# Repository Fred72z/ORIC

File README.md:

# BUS ORIC

Ensemble de platines pouvant se connecter sur un boitier principal connecté au port EXPANSION de l'oric.

# EXP CARTOUCHE
Extension permettant de remplacer la ROM interne par une cartouche ROM externe

# TELESTRAT II et TELESTRAT III

Nouvelles machines TELESTRAT.
(Dans la série si vous ne pouvez pas la trouver, faites la vous-même :)).

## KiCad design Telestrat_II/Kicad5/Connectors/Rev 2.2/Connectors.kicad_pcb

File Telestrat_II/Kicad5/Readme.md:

# Platine principale

# Platine connecteurs

# Front USB
Cette platine reprend les composants de l'afficheur du GOTEK et un connecteur USB du boitier. Il reste à ajouter 2 boutons 6x6x8mm.

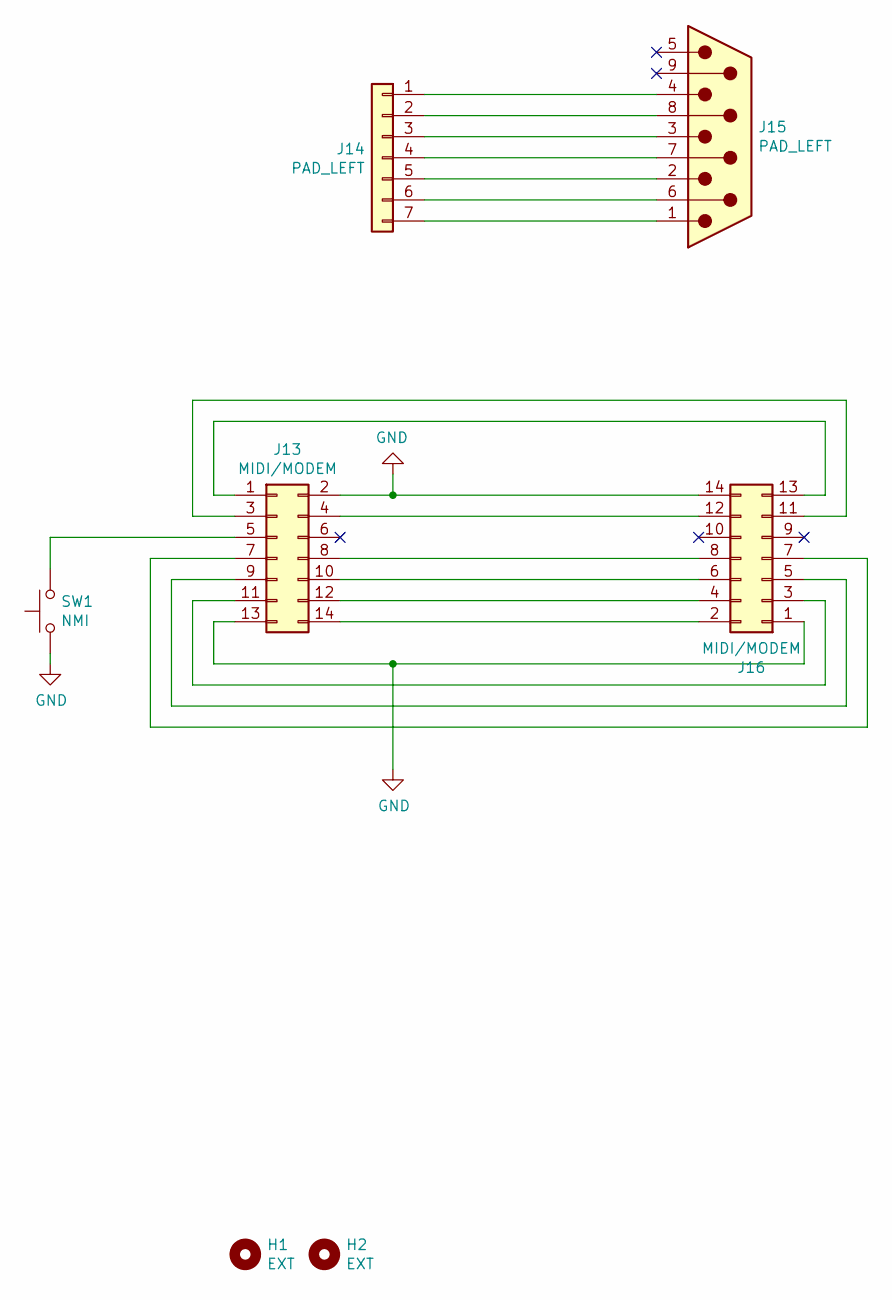
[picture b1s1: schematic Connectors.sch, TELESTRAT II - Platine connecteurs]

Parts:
H1, H2: EXT; MountingHole_3.2mm_M3_DIN965_Pad
J13: MIDI/MODEM; PinHeader_2x07_P2.54mm_Vertical
J14: PAD_LEFT; PinHeader_1x07_P2.54mm_Vertical
J15: PAD_LEFT; DSUB-9_Male_Horizontal_P2.77x2.84mm_EdgePinOffset8mm_Housed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
J16: MIDI/MODEM; IDC-Header_2x07_P2.54mm_Horizontal
SW1: NMI; SW_Tactile_SPST_Angled_PTS645Vx58-2LFS

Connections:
GND: J13.2, J13.13, J16.1, J16.14, SW1.1
unnamed: J13.1, J16.13
unnamed: J13.3, J16.11
unnamed: J13.4, J16.12
unnamed: J13.5, SW1.2
unnamed: J13.7, J16.7
unnamed: J13.8, J16.8
unnamed: J13.9, J16.5
unnamed: J13.10, J16.6
unnamed: J13.11, J16.3
unnamed: J13.12, J16.4
unnamed: J13.14, J16.2
unnamed: J14.1, J15.4
unnamed: J14.2, J15.8
unnamed: J14.3, J15.3
unnamed: J14.4, J15.7
unnamed: J14.5, J15.2
unnamed: J14.6, J15.6
unnamed: J14.7, J15.1

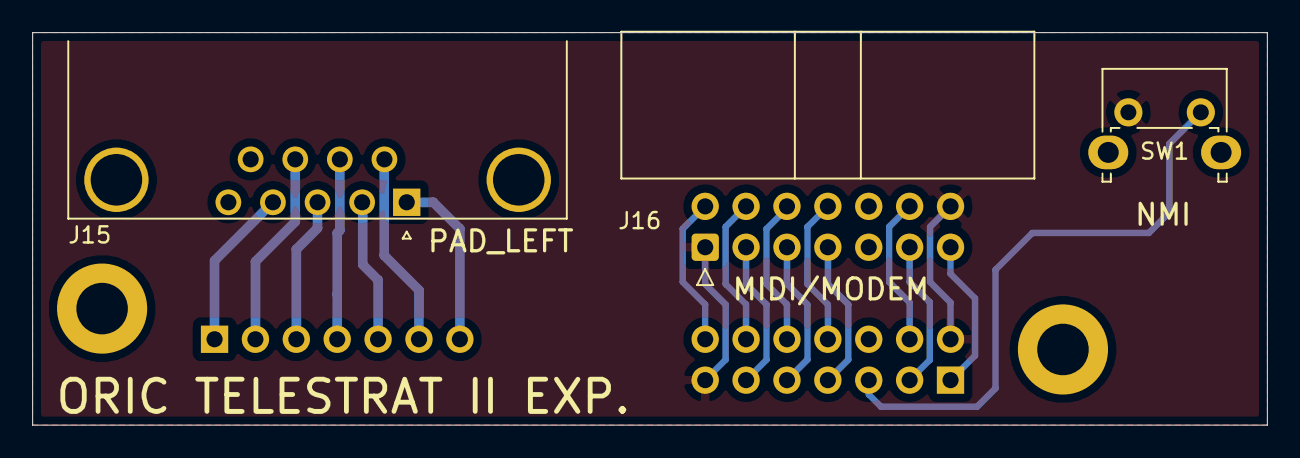
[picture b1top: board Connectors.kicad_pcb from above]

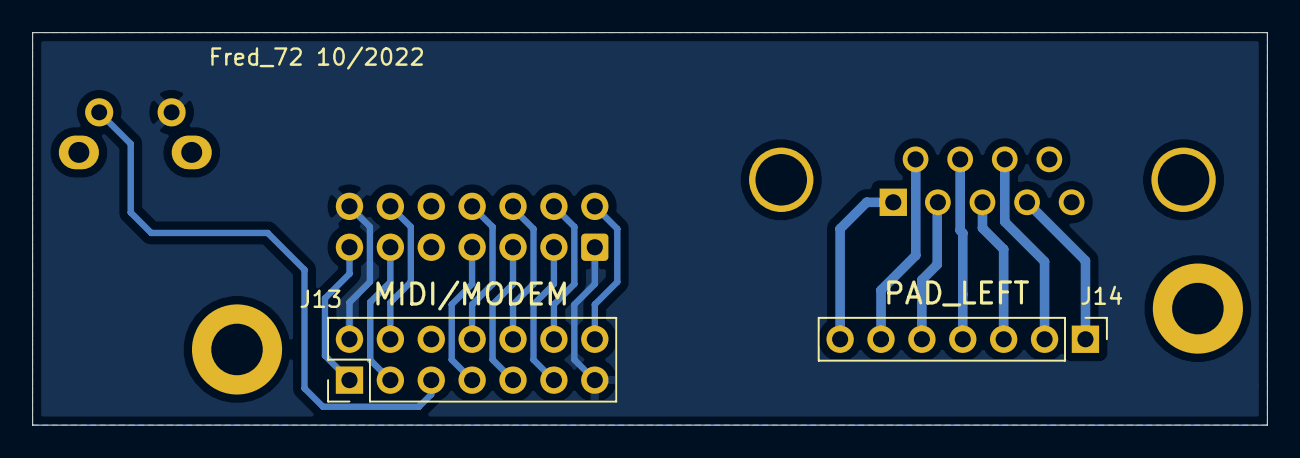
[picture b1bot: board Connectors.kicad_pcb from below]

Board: 2 copper layers, 76.7 x 24.4 mm, 7 parts (2 on the bottom side), 19 nets.

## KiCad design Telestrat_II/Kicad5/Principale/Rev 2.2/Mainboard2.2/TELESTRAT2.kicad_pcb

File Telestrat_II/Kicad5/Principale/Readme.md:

# Platine principale

La dernière révision 2.2 adopte un circuit reset indépendant du CPLD et un connecteur IDC14 pour le clavier.
C'est la dernière version, il n'y en aura pas d'autres.

La platine connecteurs a été légérement modifiée et doit correspondre à cette version.
Le code CPLD est identique à la version 2.1.

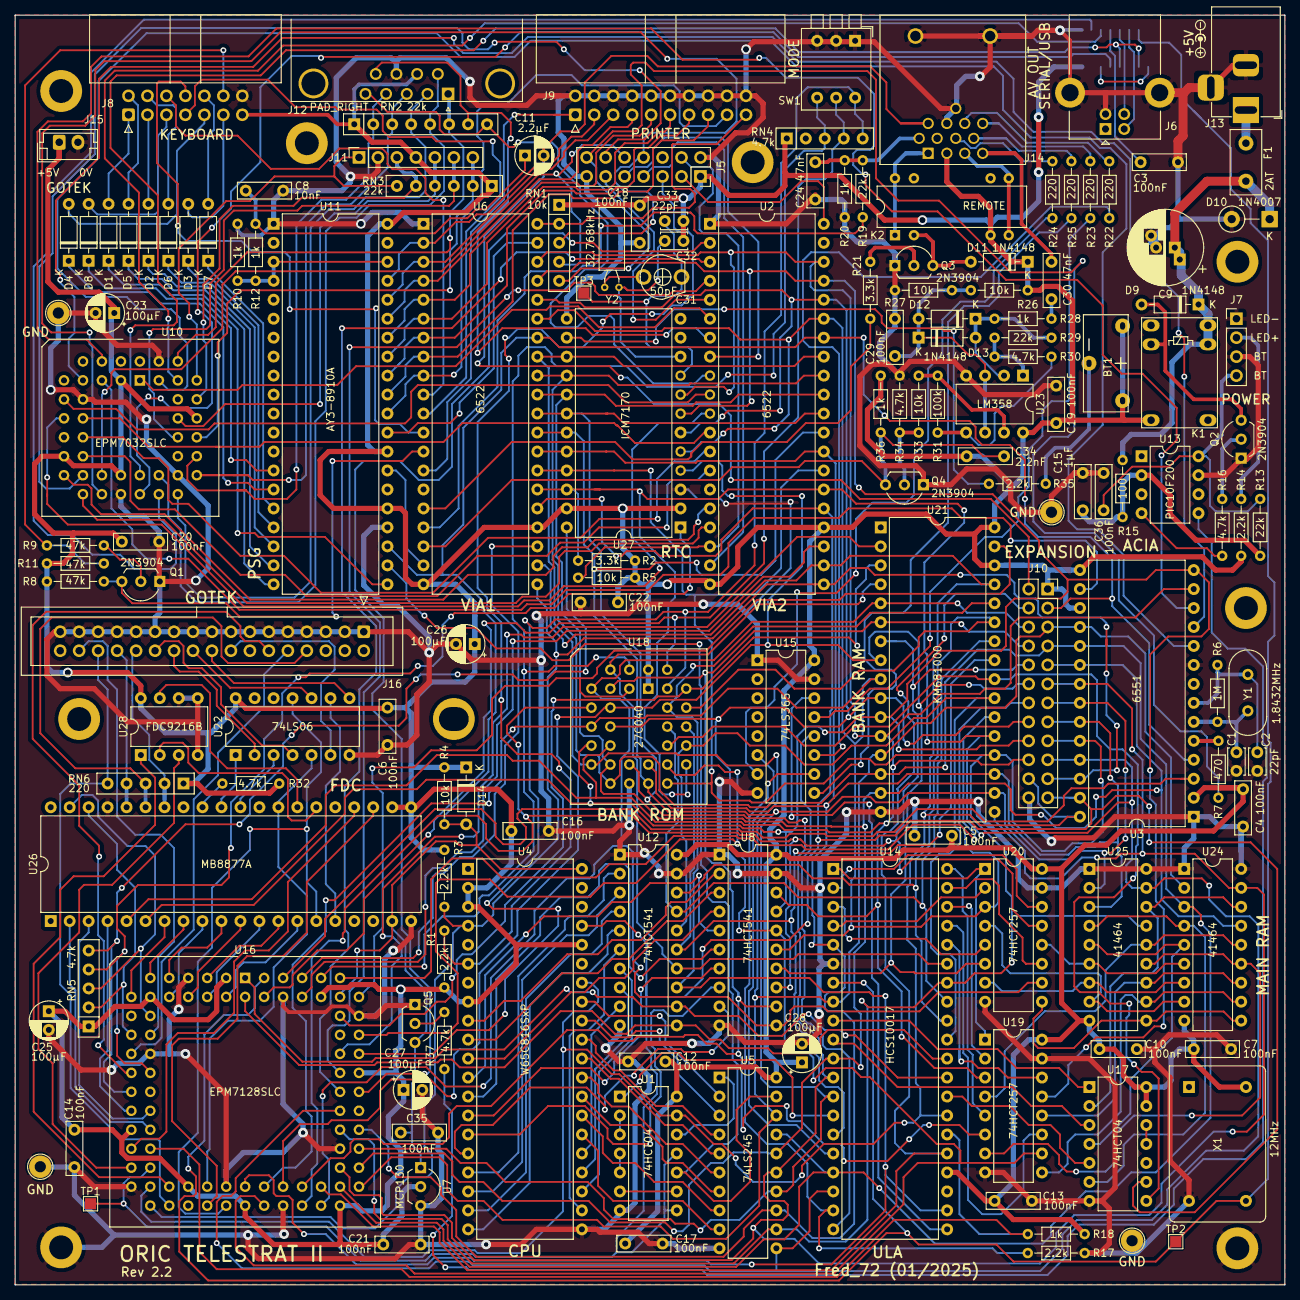
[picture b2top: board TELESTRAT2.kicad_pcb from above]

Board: 2 copper layers, 170.0 x 170.0 mm, 162 parts (1 on the bottom side), 266 nets.

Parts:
BT1: 3V; Battery_Holder_Half_Round_CR2032
C1, C2, C32, C33: 22pF; C_Disc_D3.4mm_W2.1mm_P2.50mm
C3, C4, C5, C6, C7, C10, C12, C13, C14, C16, C17, C18, C19, C20, C21, C22, C29, C35, C36: 100nF; C_Rect_L7.0mm_W2.0mm_P5.00mm
C8: 10nF; C_Rect_L7.0mm_W2.0mm_P5.00mm
C9: 1000µF; CP_Radial_D10.0mm_P2.50mm_P5.00mm
C11: 2.2µF; CP_Radial_D5.0mm_P2.50mm
C15: 1µF; C_Rect_L7.0mm_W2.0mm_P5.00mm
C23, C25, C26, C27, C28: 100µF; CP_Radial_D5.0mm_P2.50mm
C24, C30: 47nF; C_Rect_L7.0mm_W2.0mm_P5.00mm
C31: 50pF; Trimmer_Cap_TZ03F
C34: 2.2nF; C_Rect_L7.0mm_W2.0mm_P5.00mm
D1, D2, D3, D4, D5, D6, D7, D8, D9, D11, D12, D13, D14: 1N4148; D_DO-35_SOD27_P7.62mm_Horizontal
D10: 1N4007; D_DO-41_SOD81_P5.08mm_Vertical_KathodeUp
F1: 2AT; Fuse_Littelfuse_395Series
H1, H2: EXT; MountingHole_3.2mm_M3_DIN965_Pad
H3, H4: GOTEK; MountingHole_3.2mm_M3_DIN965_Pad
H5: EXP; MountingHole_3.2mm_M3_DIN965_Pad
H6: ITX1; MountingHole_3.2mm_M3_DIN965_Pad
H7: ITX2; MountingHole_3.2mm_M3_DIN965_Pad
H8: ITX3; MountingHole_3.2mm_M3_DIN965_Pad
H9: ITX4; MountingHole_3.2mm_M3_DIN965_Pad
J1, J2, J3, J4: GND; TestPoint_Loop_D2.54mm_Drill1.5mm_Beaded
J5: MIDI/MODEM; PinSocket_2x07_P2.54mm_Vertical
J6: SERIAL/USB; USB_B_Lumberg_2411_02_Horizontal
J7: POWER; PinHeader_1x04_P2.54mm_Vertical
J8: KEYBOARD; IDC-Header_2x07_P2.54mm_Horizontal
J9: PRINTER; IDC-Header_2x10_P2.54mm_Horizontal
J10: EXPANSION; PinSocket_2x12_P2.54mm_Vertical
J11: PAD_LEFT; PinSocket_1x07_P2.54mm_Vertical
J12: PAD_RIGHT; DSUB-9_Male_Horizontal_P2.77x2.84mm_EdgePinOffset8mm_Housed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
J13: +5V; BarrelJack_Horizontal
J14: AV OUT; DIN-13
J15: GOTEK; JST_EH_B2B-EH-A_1x02_P2.50mm_Vertical
J16: GOTEK; IDC-Header_2x17_P2.54mm_Vertical
K1: 5V; Relay_SPDT_HJR-4102
K2: REMOTE; Relay_StandexMeder_DIP_LowProfile
Q1, Q2, Q3, Q4, Q5: 2N3904; TO-92L_Inline_Wide
R1, R3, R14, R17, R35: 2.2k; R_Axial_DIN0204_L3.6mm_D1.6mm_P7.62mm_Horizontal
R2, R21: 3.3k; R_Axial_DIN0204_L3.6mm_D1.6mm_P7.62mm_Horizontal
R4, R5, R26, R27, R33: 10k; R_Axial_DIN0204_L3.6mm_D1.6mm_P7.62mm_Horizontal
R6: 1M; R_Axial_DIN0204_L3.6mm_D1.6mm_P7.62mm_Horizontal
R7: 470; R_Axial_DIN0204_L3.6mm_D1.6mm_P7.62mm_Horizontal
R8, R9, R11: 47k; R_Axial_DIN0204_L3.6mm_D1.6mm_P7.62mm_Horizontal
R10, R12, R18, R20, R28, R36: 1k; R_Axial_DIN0204_L3.6mm_D1.6mm_P7.62mm_Horizontal
R13, R19, R29: 22k; R_Axial_DIN0204_L3.6mm_D1.6mm_P7.62mm_Horizontal
R15: 100; R_Axial_DIN0204_L3.6mm_D1.6mm_P7.62mm_Horizontal
R16, R30, R32, R34, R37: 4.7k; R_Axial_DIN0204_L3.6mm_D1.6mm_P7.62mm_Horizontal
R22, R23, R24, R25: 220; R_Axial_DIN0204_L3.6mm_D1.6mm_P7.62mm_Horizontal
R31: 100k; R_Axial_DIN0204_L3.6mm_D1.6mm_P7.62mm_Horizontal
RN1: 10k; R_Array_SIP5
RN2: 22k; R_Array_SIP8
RN3: 22k; R_Array_SIP6
RN4, RN5: 4.7k; R_Array_SIP5
RN6: 220; R_Array_SIP5
SW1: MODE; SW_DIP_SPSTx03_Piano_10.8x9.18mm_W7.62mm_P2.54mm
TP1: PHI2; TestPoint_Pad_1.5x1.5mm
TP2: 12MHZ; TestPoint_Pad_1.5x1.5mm
TP3: 32.768kHz; TestPoint_Pad_1.5x1.5mm
U1, U17: 74HCT04; DIP-14_W7.62mm
U2, U6: 6522; DIP-40_W15.24mm
U3: 6551; DIP-28_W15.24mm
U4: W65C816SxP; DIP-40_W15.24mm
U5: 74LS245; DIP-20_W7.62mm
U7: MCP130; TO-92L_Inline_Wide
U8, U12: 74HCT541; DIP-20_W7.62mm
U9: CH340G; SOIC-16_3.9x9.9mm_P1.27mm
U10: EPM7032SLC; PLCC-44_THT-Socket
U11: AY3-8910A; DIP-40_W15.24mm
U13: PIC10F200; DIP-8_W7.62mm
U14: HCS10017; DIP-40_W15.24mm
U15: 74LS365; DIP-16_W7.62mm
U16: EPM7128SLC; PLCC-84_THT-Socket
U18: 27C040; PLCC-32_THT-Socket
U19, U20: 74HCT257; DIP-16_W7.62mm
U21: KM681000; DIP-32_W15.24mm
U22: 74LS06; DIP-14_W7.62mm
U23: LM358; DIP-8_W7.62mm
U24, U25: 41464; DIP-18_W7.62mm
U26: MB8877A; DIP-40_W15.24mm
U27: ICM7170; DIP-24_W15.24mm
U28: FDC9216B; DIP-8_W7.62mm
X1: 12MHz; Oscillator_DIP-14
Y1: 1.8432MHz; Crystal_HC49-4H_Vertical
Y2: 32.768kHz; Crystal_C38-LF_D3.0mm_L8.0mm_Horizontal

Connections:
+5V: C9.1, D9.1, D10.1, F1.2, K1.5, K1.6, R15.2
-BATT: R35.2, U27.14
/A0: J10.20, U2.38, U3.13, U6.38, U8.18, U18.12, U19.3, U21.12, U26.5, U27.8
/A1: J10.18, U2.37, U3.14, U6.37, U8.17, U18.11, U19.13, U21.11, U26.6, U27.7
/A2: J10.16, U2.36, U6.36, U8.16, U16.45, U18.10, U19.10, U21.10, U27.6
/A3: J10.14, U2.35, U6.35, U8.15, U16.46, U18.9, U20.3, U21.9, U27.5
/A4: J10.12, U8.14, U16.48, U18.8, U20.6, U21.8, U27.4
/A5: J10.10, U8.13, U16.49, U18.7, U20.13, U21.7
/A6: J10.8, U8.12, U16.50, U18.6, U19.6, U21.6
/A7: J10.6, U8.11, U16.51, U18.5, U20.10, U21.5
/A8: U12.18, U14.32, U18.27, U21.27
/A9: U12.17, U14.33, U18.26, U21.26
/A10: U12.16, U14.31, U18.23, U21.23
/A11: U12.15, U14.15, U18.25, U21.25
/A12: U12.14, U14.35, U18.4, U21.4
/A13: U12.13, U14.22, U16.44, U18.28, U21.28
/A14: U12.12, U14.29, U16.1
/A15: U12.11, U14.30, U16.2
/BAUD_RATE: J5.14, R7.1, RN1.5
/Bleu: R23.2, U15.13
/CARRIER: J5.8, RN1.3, U10.20
/CLK_1MHz: U16.28, U26.24
/CLK_4MHz: U16.30, U28.3
/CLK_12MHz: TP2.1, U9.7, U14.7, U16.83, X1.8
/COL0: D1.2, J8.1
/COL1: D5.2, J8.2
/COL2: D2.2, J8.3
/COL3: D6.2, J8.4
/COL4: D3.2, J8.11
/COL5: D7.2, J8.10
/COL6: D4.2, J8.9
/COL7: D8.2, J8.5
/CPU_A0: U4.9, U8.2
/CPU_A1: U4.10, U8.3
/CPU_A2: U4.11, U8.4
/CPU_A3: U4.12, U8.5
/CPU_A4: U4.13, U8.6
/CPU_A5: U4.14, U8.7
/CPU_A6: U4.15, U8.8
/CPU_A7: U4.16, U8.9
/CPU_A8: U4.17, U12.2
/CPU_A9: U4.18, U12.3
/CPU_A10: U4.19, U12.4
/CPU_A11: U4.20, U12.5
/CPU_A12: U4.22, U12.6
/CPU_A13: U4.23, U12.7
/CPU_A14: U4.24, U12.8
/CPU_A15: U4.25, U12.9
/D0: J10.5, U2.33, U3.18, U5.18, U6.33, U14.8, U16.54, U18.13, U21.13, U24.2, U27.15
/D1: J10.7, U2.32, U3.19, U5.17, U6.32, U14.17, U16.55, U18.14, U21.14, U24.3, U27.16
/D2: J10.9, U2.31, U3.20, U5.16, U6.31, U14.11, U16.56, U18.15, U21.15, U24.15, U27.17
/D3: J10.11, U2.30, U3.21, U5.15, U6.30, U14.12, U16.57, U18.17, U21.17, U24.17, U27.18
/D4: J10.13, U2.29, U3.22, U5.14, U6.29, U14.13, U16.58, U18.18, U21.18, U25.2, U27.19
/D5: J10.15, U2.28, U3.23, U5.13, U6.28, U14.5, U16.60, U18.19, U21.19, U25.3, U27.20
/D6: J10.17, U2.27, U3.24, U5.12, U6.27, U14.34, U16.61, U18.20, U21.20, U25.15, U27.21
/D7: J10.19, R2.1, U2.26, U3.25, U5.11, U6.26, U14.18, U16.63, U18.21, U21.21, U25.17, U27.22
/DAT_IN: J5.10, RN1.4, U10.21
/DAT_OUT: J5.12, U10.19
/DF0: U16.12, U26.7
/DF1: U16.11, U26.8
/DF2: U16.10, U26.9
/DF3: U16.9, U26.10
/DF4: U16.8, U26.11
/DF5: U16.6, U26.12
/DF6: U16.5, U26.13
/DF7: U16.4, U26.14
/FDC_DRQ: RN5.2, U16.16, U26.38
/FDC_IRQ: RN5.3, U16.15, U26.39
/HLD: U16.40, U22.5, U26.28
/HLT: U16.39, U26.23
/IN: C30.2, J14.4
/K7_IN: C34.1, Q4.3, R36.2, U6.18
/K7_OUT: R19.2, U6.17
/KBD_AD0: J8.6, U6.10
/KBD_AD1: J8.7, U6.11
/KBD_AD2: J8.8, U6.12
/KBD_D: Q1.3, R8.1, U6.13
/MA0: U14.38, U19.2
/MA1: U14.36, U19.14
/MA2: U14.37, U19.11
/MA3: U14.4, U20.2
/MA4: U14.3, U20.5
/MA5: U14.2, U20.14
/MA6: U14.40, U19.5
/MA7: U14.39, U20.11
/MODE1: RN4.3, SW1.4, U16.77, U18.2
/MODE2: RN4.4, SW1.5, U16.84, U18.30
/MODE3: RN4.5, SW1.6, U16.68, U18.31
/OUT: C24.1, J14.5, R19.1, R20.2
/PA0: J9.3, U6.2, U11.37
/PA0_2: U2.2, U16.64
/PA1: J9.5, U6.3, U11.36
/PA1_2: U2.3, U16.65
/PA2: J9.7, U6.4, U11.35
/PA2_2: U2.4, U16.67
/PA3: J9.9, U6.5, U11.34
/PA4: J9.11, U6.6, U11.33
/PA5: J9.13, U6.7, U11.32
/PA6: J9.15, U6.8, U11.31
/PA7: J9.17, U6.9, U11.30
/PHI0: U1.1, U14.14
/PHI1: U1.10, U5.19, U11.22
/PHI2: J10.23, TP1.1, U1.8, U1.11, U2.25, U3.27, U4.37, U6.25, U16.31, U17.9
/RDB: U16.36, U28.1
/RD_DATA: J16.30, RN6.5, U16.35
/RE: U16.24, U26.4
/REMOTE: R21.2, U6.16
/RST: R37.2, U13.5
/R_~W: J10.22, U1.13, U2.22, U3.28, U4.34, U6.22, U14.27, U16.34, U21.29
/Rouge: R25.2, U15.9
/SIDE: J16.32, U16.17
/SOUND: C11.2, J10.2, J14.9
/STEP: U16.41, U22.11, U26.15
/SYNC: R24.2, U15.7
/TIR2: J12.5, RN2.8, U2.9
/TIR3: J12.9, RN2.7, U2.7
/Vert: R22.2, U15.11
/WE: U16.27, U26.2
/WR_DATA: J16.22, U22.2
/~ACIA: U3.3, U16.81
/~ACK: J9.19, RN1.2, U6.40
/~CAS: U17.2, U24.16, U25.16
/~DIR: J16.18, U22.8
/~DS0: J16.10, U16.18
/~DS1: J16.12, U16.20
/~FDC: U16.25, U26.3
/~INDEX: J16.8, RN6.3, U26.35
/~IRQ: J10.21, R3.1, U2.21, U3.26, U4.4, U6.21, U16.33
/~I_O: J10.4, U14.25, U16.52
/~MAP: R18.2, U14.26, U16.29
/~MOTOR: J16.16, U22.6
/~NMI: J5.5, R1.1, U4.6
/~RAS: U17.4, U24.5, U25.5
/~RD_RTC: RN5.5, U16.22, U27.24
/~RESET: C35.2, D14.2, J10.3, Q5.3, R4.1, U2.34, U3.4, U4.40, U6.34, U7.1, U11.23, U16.76, U26.19
/~STB: J9.1, U6.14
/~STEP: J16.20, U22.10
/~TRK0: J16.26, RN6.2, U26.34
/~VIA1: U6.23, U16.79
/~VIA2: U2.23, U16.80
/~WG: J16.24, U22.4
/~WPROT: J16.28, RN6.4, U26.36
/~WR_RTC: RN5.4, U16.21, U27.1
GND: C1.2, C2.2, C3.2, C4.2, C5.2, C6.2, C7.2, C8.1, C9.2, C10.2, C12.2, C13.2, C14.2, C15.1, C16.2, C17.2, C18.2, C19.2, C20.2, C21.2, C22.2, C23.2, C24.2, C25.2, C26.2, C27.2, C28.2, C29.2, C35.1, C36.1, D10.2, H6.1, H9.1, J1.1, J2.1, J3.1, J4.1, J5.2, J5.13, J6.4, J6.5, J7.1, J7.3, J8.14, J9.2, J9.4, J9.6, J9.8, J9.10, J9.12, J9.14, J9.16, J9.18, J9.20, J10.24, J11.2, J12.8, J13.2, J13.3, J14.10, J14.13, J14.E1, J14.E2, J15.2, J16.1, J16.3, J16.5, J16.7, J16.9, J16.11, J16.13, J16.15, J16.17, J16.19, J16.21, J16.23, J16.25, J16.27, J16.29, J16.31, J16.33, Q1.1, Q2.1, Q3.1, Q4.1, Q5.1, R10.2, R17.2, R20.1, R27.2, R34.1, SW1.1, SW1.2, SW1.3, U1.7, U2.1, U3.1, U3.9, U4.21, U5.10, U6.1, U7.3, U8.1, U8.10, U8.19, U9.1, U10.10, U10.22, U10.30, U10.42, U11.1, U11.24, U12.1, U12.10, U12.19, U13.7, U14.6, U15.1, U15.8, U15.15, U16.7, U16.19, U16.32, U16.42, U16.47, U16.59, U16.72, U16.82, U17.7, U18.16, U19.8, U19.15, U20.8, U20.15, U21.16, U22.7, U23.4, U24.1, U24.18, U25.1, U25.18, U26.20, U26.37, U27.3, U27.13, U28.4, U28.5, U28.6, X1.7
unnamed: BT1.2, R35.1
unnamed: C1.1, R6.1, U3.6, Y1.2
unnamed: C2.1, R6.2, U3.7, Y1.1
unnamed: C3.1, U9.4
unnamed: C8.2, C11.1, R12.1
unnamed: C29.1, D12.2, D13.1, R26.2, R27.1, U23.3, U23.6
unnamed: C30.1, R28.1
unnamed: C31.1, Y2.2
unnamed: C31.2, C33.1, TP3.1, U27.9
unnamed: C32.1, U27.10, Y2.1
unnamed: C36.2, J7.4, R13.1, U13.8
unnamed: D1.1, U11.21
unnamed: D2.1, U11.19
unnamed: D3.1, U11.17
unnamed: D4.1, U11.15
unnamed: D5.1, U11.20
unnamed: D6.1, U11.18
unnamed: D7.1, U11.16
unnamed: D8.1, U11.14
unnamed: D9.2, K1.8, Q2.3
unnamed: D11.2, K2.2, Q3.3
unnamed: D12.1, D13.2, R28.2, R29.2, U23.2
unnamed: F1.1, J13.1
unnamed: J5.3, U2.40
unnamed: J5.4, R5.1, U2.18
unnamed: J5.7, U2.19
unnamed: J5.9, U2.8
unnamed: J5.11, U2.5
unnamed: J6.2, U9.6
unnamed: J6.3, U9.5
unnamed: J7.2, R14.2
unnamed: J8.12, R9.1, R11.1
unnamed: J11.1, RN3.6, U10.39
unnamed: J11.3, RN3.5, U10.37
unnamed: J11.5, RN3.4, U10.36
unnamed: J11.6, RN3.3, U10.34
unnamed: J11.7, RN3.2, U10.33
unnamed: J12.1, RN2.6, U10.40
unnamed: J12.2, RN2.4, U10.28
unnamed: J12.3, RN2.3, U10.29
unnamed: J12.4, RN2.2, U10.31
unnamed: J12.6, RN2.5, U10.27
unnamed: J14.1, K2.1, K2.14
unnamed: J14.3, K2.7, K2.8
unnamed: J14.7, R24.1
unnamed: J14.8, R25.1
unnamed: J14.11, R22.1
unnamed: J14.12, R23.1
unnamed: Q1.2, R9.2
unnamed: Q2.2, R16.1
unnamed: Q3.2, R21.1
unnamed: Q4.2, R33.1, R34.2
unnamed: Q5.2, R37.1
unnamed: R7.2, U3.5
unnamed: R10.1, R12.2, U11.3, U11.4, U11.38
unnamed: R16.2, U13.4
unnamed: R17.1, U14.19, U15.10
unnamed: R29.1, R30.2, U23.1
unnamed: R30.1, R31.2, U23.5
unnamed: R31.1, R33.2, U23.7
unnamed: R32.2, U26.32
unnamed: U1.2, U1.3
unnamed: U1.4, U1.5
unnamed: U1.6, U1.9
unnamed: U1.12, U5.1
unnamed: U4.26, U5.9
unnamed: U4.27, U5.8
unnamed: U4.28, U5.7
unnamed: U4.29, U5.6
unnamed: U4.30, U5.5
unnamed: U4.31, U5.4
unnamed: U4.32, U5.3
unnamed: U4.33, U5.2
unnamed: U9.9, U9.14
unnamed: U2.6, U10.1
unnamed: U3.12, U10.4
unnamed: U3.16, U10.5
unnamed: U3.11, U10.8
unnamed: U2.10, U10.9
unnamed: U2.11, U10.11
unnamed: U2.12, U10.12
unnamed: U2.13, U10.14
unnamed: U2.14, U10.16
unnamed: U2.16, U10.17
unnamed: U2.17, U10.18
unnamed: U9.13, U10.24
unnamed: U9.10, U9.12, U10.25
unnamed: U9.2, U10.26
unnamed: U9.3, U10.41
unnamed: U3.10, U10.43
unnamed: U6.19, U11.27
unnamed: U6.39, U11.29
unnamed: U14.1, U19.1, U20.1
unnamed: U14.9, U17.1
unnamed: U14.10, U17.3
unnamed: U14.16, U15.6
unnamed: U14.20, U15.12
unnamed: U14.21, U15.14
unnamed: U14.28, U17.5
unnamed: U16.69, U21.2
unnamed: U16.70, U18.22
unnamed: U16.73, U18.29, U21.3
unnamed: U16.74, U18.3, U21.31
unnamed: U16.75, U21.22
unnamed: U17.6, U24.4, U25.4
unnamed: U17.8, U18.24, U21.24
unnamed: U17.11, U17.12
unnamed: U19.4, U24.14, U25.14
unnamed: U19.7, U24.13, U25.13
unnamed: U19.9, U24.11, U25.11
unnamed: U19.12, U24.12, U25.12
unnamed: U20.4, U24.8, U25.8
unnamed: U20.7, U24.7, U25.7
unnamed: U20.9, U24.10, U25.10
unnamed: U20.12, U24.6, U25.6
unnamed: U22.1, U26.31
unnamed: U22.3, U26.30
unnamed: U22.9, U26.16
unnamed: U26.26, U28.2
unnamed: U26.27, U28.7
VCC: BT1.1, C4.1, C5.1, C6.1, C7.1, C10.1, C12.1, C13.1, C14.1, C16.1, C17.1, C18.1, C19.1, C20.1, C21.1, C22.1, C23.1, C25.1, C26.1, C27.1, C28.1, C32.2, C33.2, C34.2, D11.1, D14.1, J5.1, J8.13, J10.1, J11.4, J12.7, J14.2, J15.1, K1.12, K2.6, R1.2, R2.2, R3.2, R4.2, R5.2, R8.2, R11.2, R14.1, R18.1, R26.1, R32.1, R36.1, RN1.1, RN2.1, RN3.1, RN4.1, RN5.1, RN6.1, U1.14, U2.20, U2.24, U3.2, U3.15, U3.17, U4.2, U4.3, U4.8, U4.36, U5.20, U6.20, U6.24, U7.2, U8.20, U9.16, U10.3, U10.15, U10.23, U10.35, U11.25, U11.28, U11.40, U12.20, U14.24, U15.16, U16.3, U16.13, U16.26, U16.38, U16.43, U16.53, U16.66, U16.78, U17.13, U17.14, U18.1, U18.32, U19.16, U20.16, U21.30, U21.32, U22.14, U23.8, U24.9, U25.9, U26.21, U26.22, U27.2, U27.23, U28.8, X1.14
VCCQ: C15.2, R13.2, R15.1, U13.2

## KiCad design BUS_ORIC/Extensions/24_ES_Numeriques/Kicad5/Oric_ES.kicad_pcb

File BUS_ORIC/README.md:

# BUS_ORIC
Platine d'extension de bus pour l'ORIC
Cette platine se branche derrière l'ORIC avec une petite nappe et reprend le principe de la carte mère MX4 sur CPC.
Elle permet d'ajouter 4 slots d'extensions à la machine tout en proposant un report du bus à l'arrière pour brancher le contrôleur microdisc.

Les extensions peuvent être alimentées à partir de l'alimentation de l'ORIC ou à partir d'une alimentation externe. Le choix se fait par un cavalier à 2 positions.
La platine possède un bouton RESET sur le côté.
Les extensions sont placées en page 3 et sont compatibles avec le contrôleur microdisc.
Les extensions à venir sont:

Synthèse vocale à MEA8000

Liaison Série ACIA

8 entrées analogiques

8 E/S numériques

16 E/S PIA

16 E/S VIA

Erebus

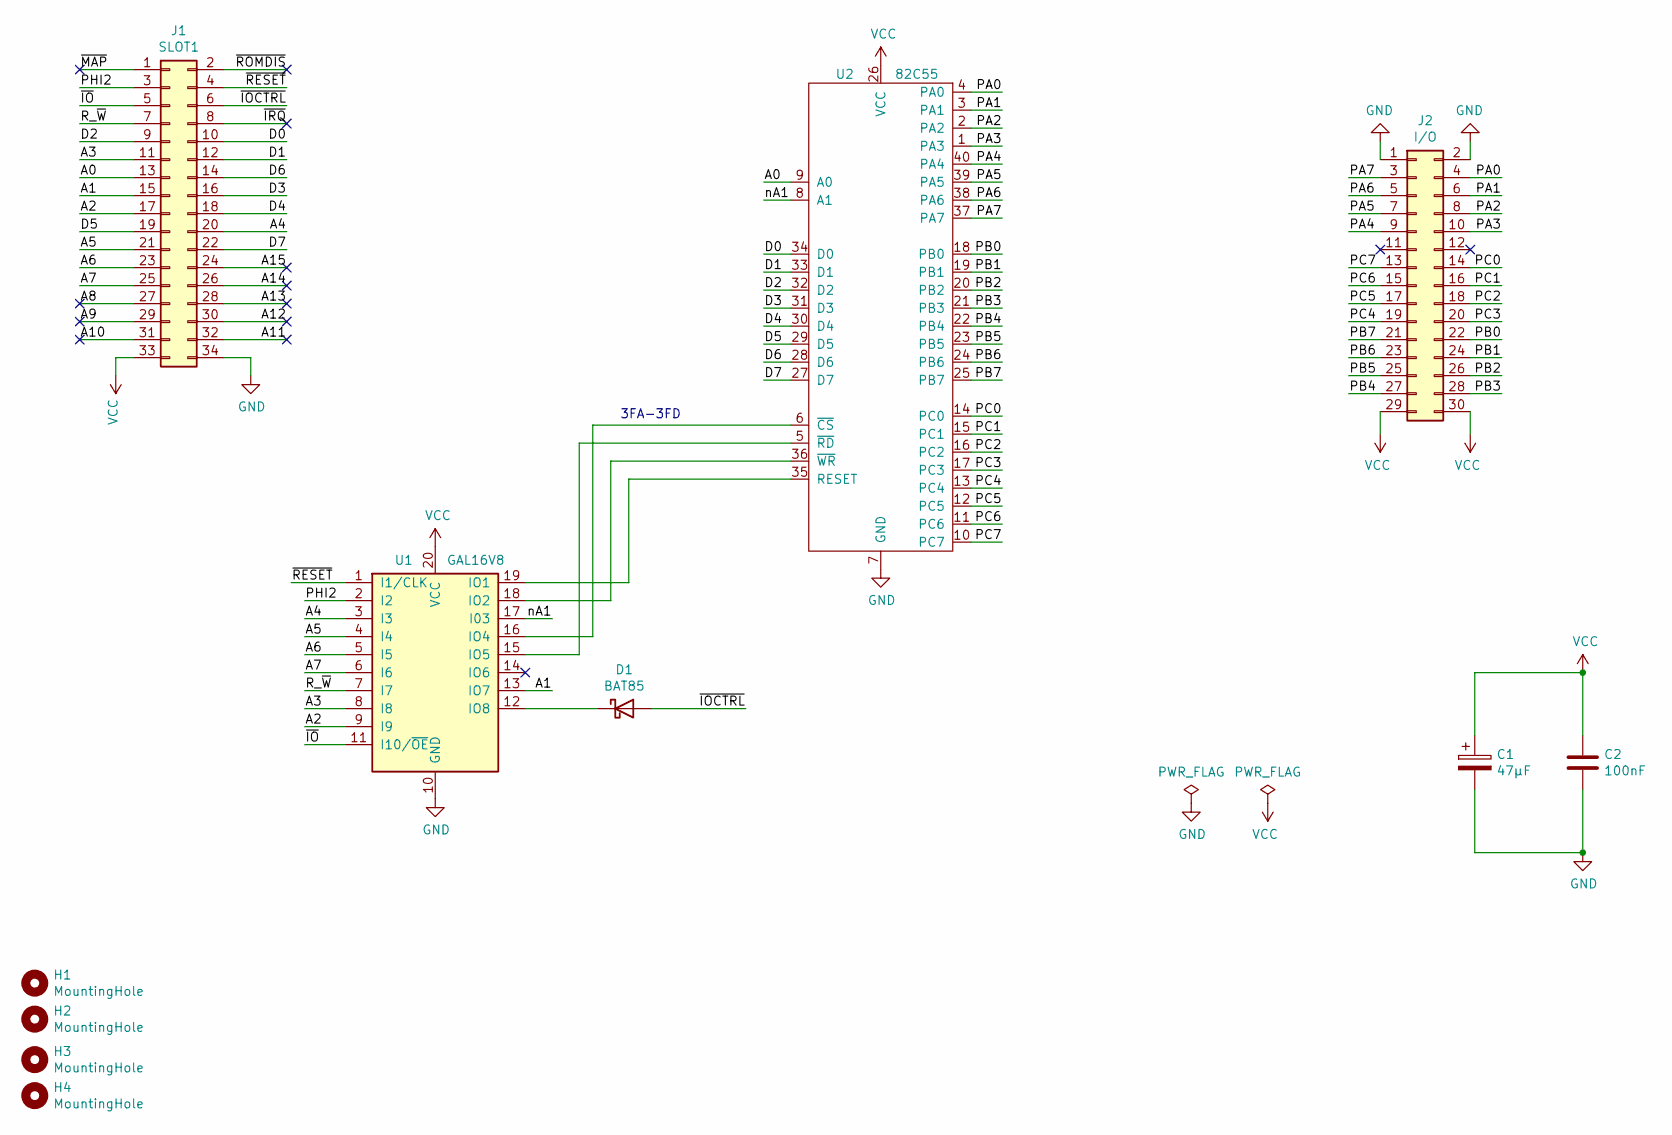
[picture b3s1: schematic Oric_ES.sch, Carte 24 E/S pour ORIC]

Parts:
C1: 47µF; CP_Radial_D5.0mm_P2.54mm_Horizontal
C2: 100nF; C_Ceramic_D5.5mm_W4mm_P5.00mm
D1: BAT85; D_DO-35_SOD27_P7.62mm_Horizontal
H1, H2, H3, H4: MountingHole; MountingHole_3.2mm_M3_DIN965_Pad
J1: SLOT1; IDC-Header_2x17_P2.54mm_Horizontal
J2: I/O; IDC-Header_2x15_P2.54mm_Horizontal
U1: GAL16V8; DIP-20_W7.62mm_LongPads
U2: 82C55; DIP-40_W15.24mm_LongPads

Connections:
/A0: J1.13, U2.9 (A0)
/A1: J1.15, U1.13 (IO7)
/A2: J1.17, U1.9 (I9)
/A3: J1.11, U1.8 (I8)
/A4: J1.20, U1.3 (I3)
/A5: J1.21, U1.4 (I4)
/A6: J1.23, U1.5 (I5)
/A7: J1.25, U1.6 (I6)
/A8: J1.27
/A9: J1.29
/A10: J1.31
/A11: J1.32
/A12: J1.30
/A13: J1.28
/A14: J1.26
/A15: J1.24
/D0: J1.10, U2.34 (D0)
/D1: J1.12, U2.33 (D1)
/D2: J1.9, U2.32 (D2)
/D3: J1.16, U2.31 (D3)
/D4: J1.18, U2.30 (D4)
/D5: J1.19, U2.29 (D5)
/D6: J1.14, U2.28 (D6)
/D7: J1.22, U2.27 (D7)
/PA0: J2.4, U2.4 (PA0)
/PA1: J2.6, U2.3 (PA1)
/PA2: J2.8, U2.2 (PA2)
/PA3: J2.10, U2.1 (PA3)
/PA4: J2.9, U2.40 (PA4)
/PA5: J2.7, U2.39 (PA5)
/PA6: J2.5, U2.38 (PA6)
/PA7: J2.3, U2.37 (PA7)
/PB0: J2.22, U2.18 (PB0)
/PB1: J2.24, U2.19 (PB1)
/PB2: J2.26, U2.20 (PB2)
/PB3: J2.28, U2.21 (PB3)
/PB4: J2.27, U2.22 (PB4)
/PB5: J2.25, U2.23 (PB5)
/PB6: J2.23, U2.24 (PB6)
/PB7: J2.21, U2.25 (PB7)
/PC0: J2.14, U2.14 (PC0)
/PC1: J2.16, U2.15 (PC1)
/PC2: J2.18, U2.16 (PC2)
/PC3: J2.20, U2.17 (PC3)
/PC4: J2.19, U2.13 (PC4)
/PC5: J2.17, U2.12 (PC5)
/PC6: J2.15, U2.11 (PC6)
/PC7: J2.13, U2.10 (PC7)
/PHI2: J1.3, U1.2 (I2)
/R_~W: J1.7, U1.7 (I7)
/nA1: U1.17 (I03), U2.8 (A1)
/~IO: J1.5, U1.11 (I10/~OE~)
/~IOCTRL: D1.2 (A), J1.6
/~IRQ: J1.8
/~MAP: J1.1
/~RESET: J1.4, U1.1 (I1/CLK)
/~ROMDIS: J1.2
GND: C1.2, C2.2, J1.34, J2.1, J2.2, U1.10 (GND), U2.7 (GND)
unnamed: D1.1 (K), U1.12 (IO8)
unnamed: U1.15 (IO5), U2.5 (~RD)
unnamed: U1.16 (IO4), U2.6 (~CS)
unnamed: U1.18 (IO2), U2.36 (~WR)
unnamed: U1.19 (IO1), U2.35 (RESET)
VCC: C1.1, C2.1, J1.33, J2.29, J2.30, U1.20 (VCC), U2.26 (VCC)

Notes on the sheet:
3FA-3FD

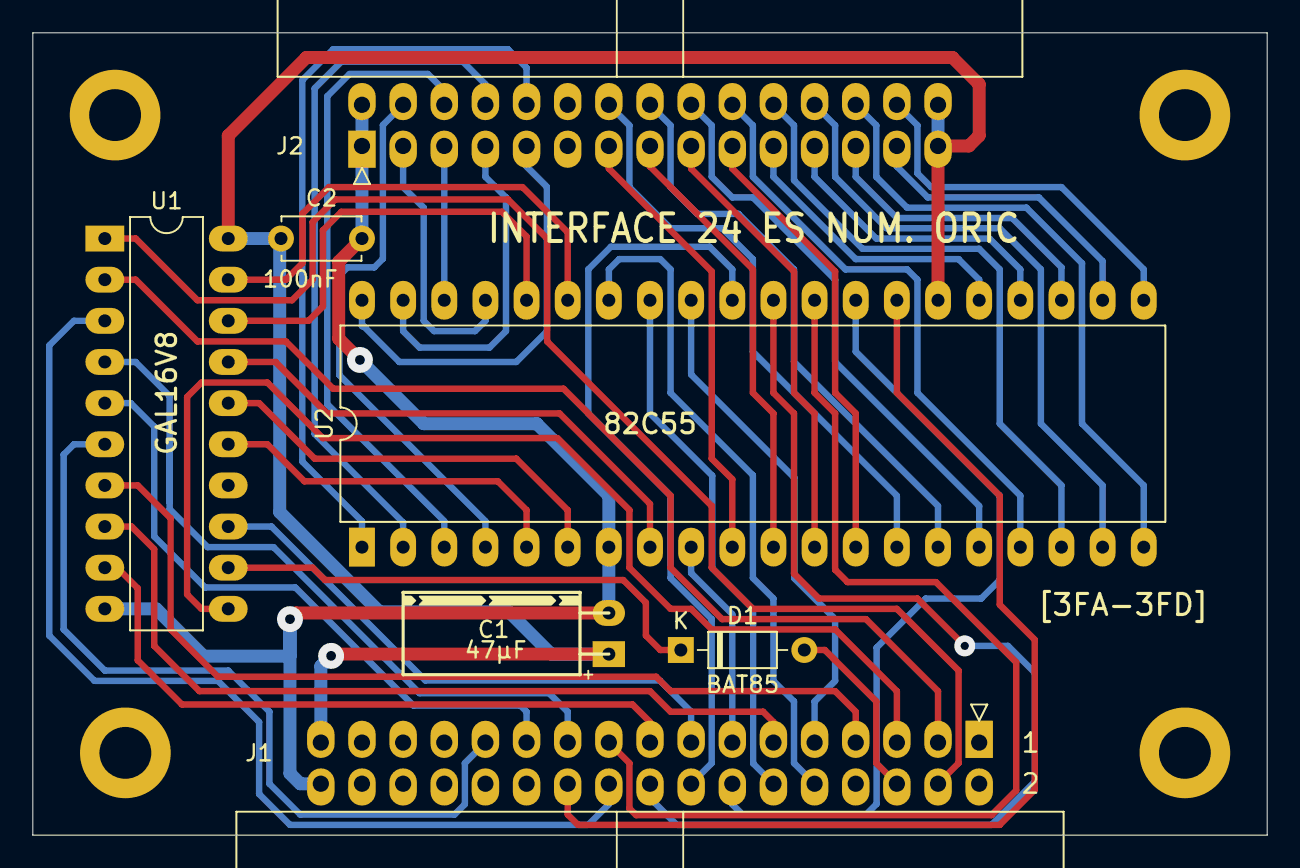
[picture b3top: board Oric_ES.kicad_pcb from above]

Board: 2 copper layers, 76.2 x 49.5 mm, 11 parts (0 on the bottom side), 53 nets.

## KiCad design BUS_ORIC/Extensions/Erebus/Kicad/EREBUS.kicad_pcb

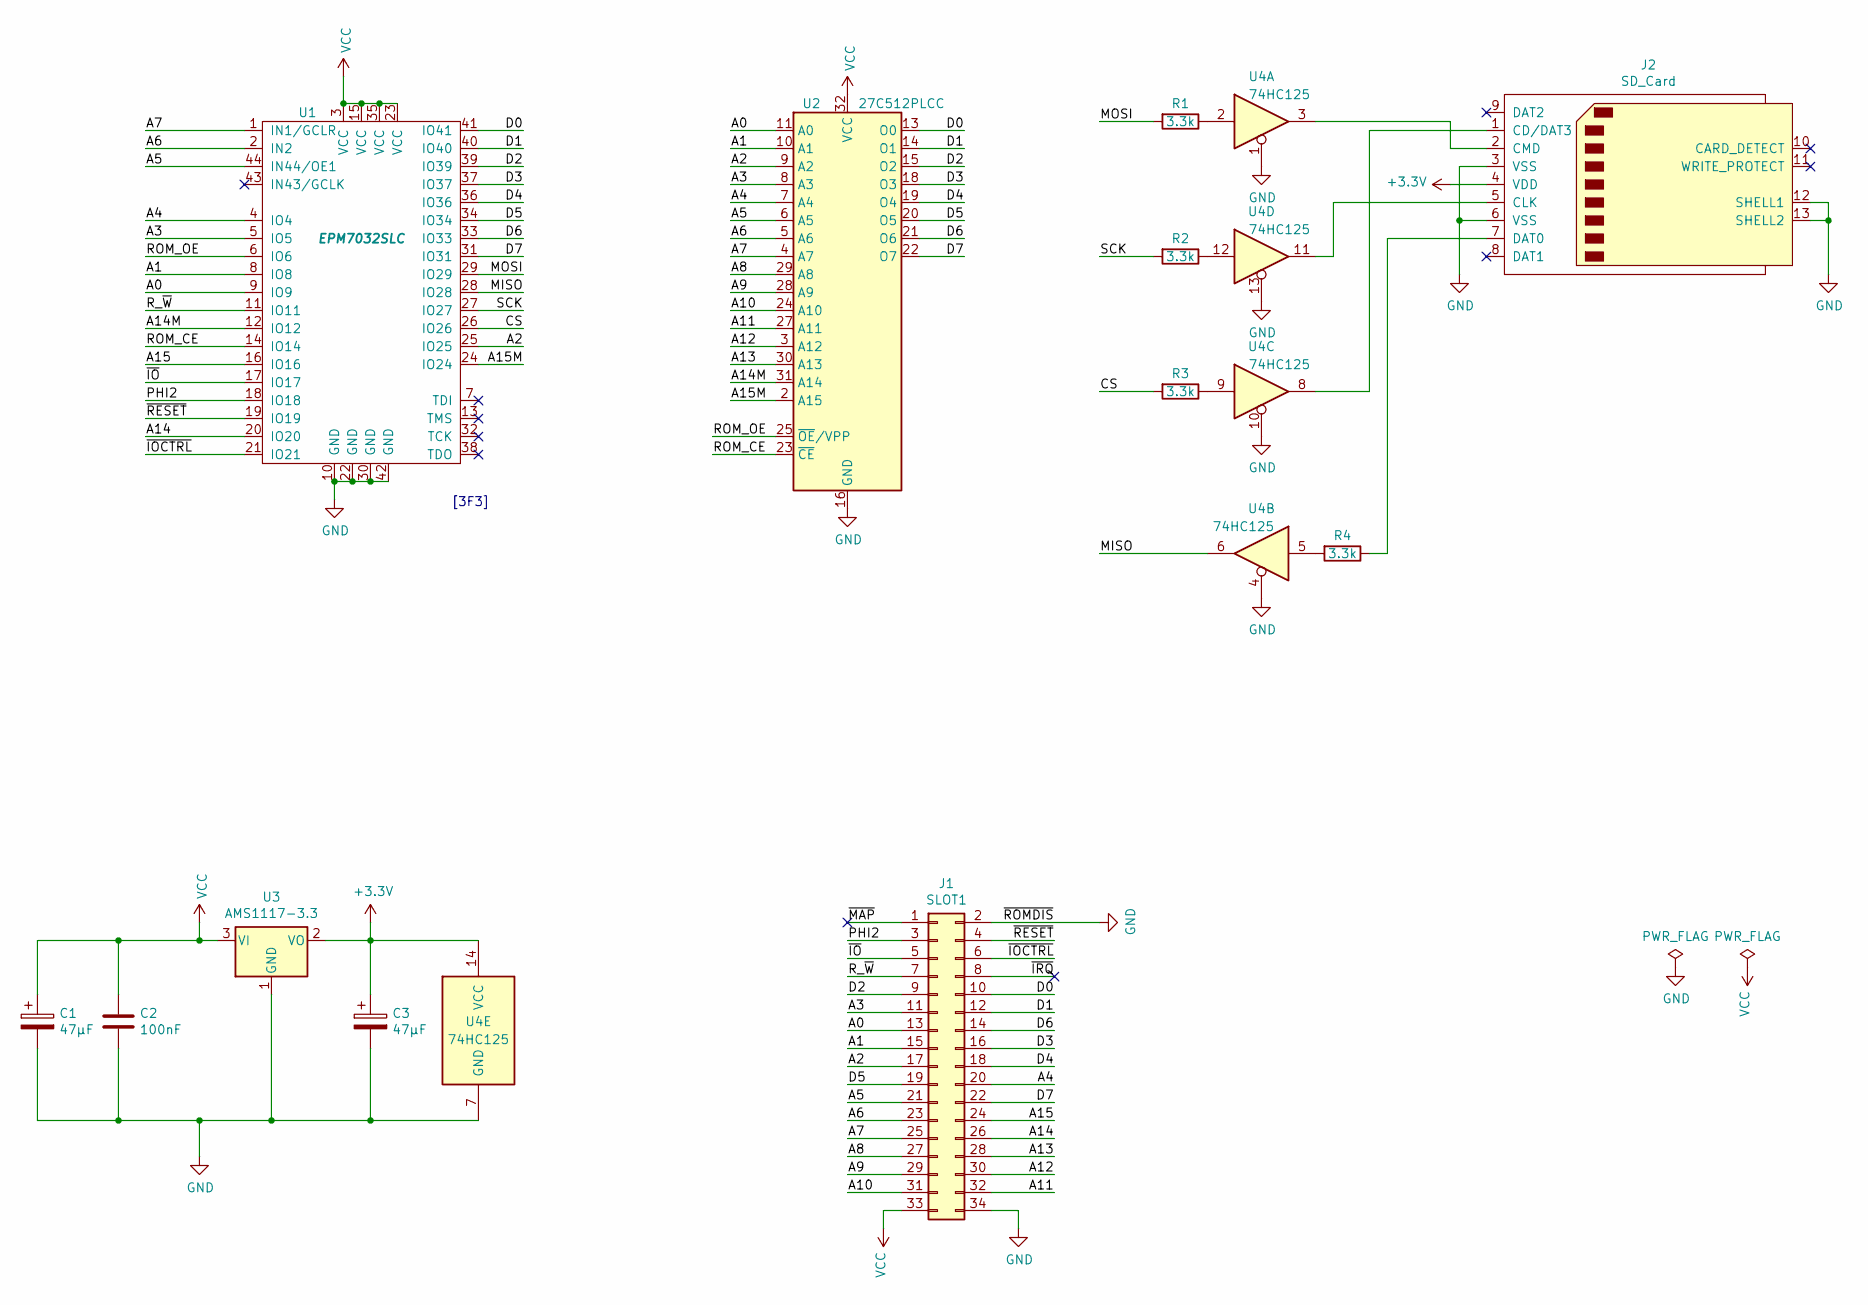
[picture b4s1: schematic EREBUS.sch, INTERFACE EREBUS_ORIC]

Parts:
C1, C3: 47µF; CP_Radial_D5.0mm_P2.00mm
C2: 100nF; C_Rect_L7.0mm_W2.0mm_P5.00mm
J1: SLOT1; IDC-Header_2x17_P2.54mm_Horizontal
J2: SD_Card; SD_Short
R1, R2, R3, R4: 3.3k; R_0805_2012Metric
U1: EPM7032SLC; PLCC-44_THT-Socket
U2: 27C512PLCC; PLCC-32_THT-Socket
U3: AMS1117-3.3; SOT-223-3_TabPin2
U4: 74HC125; SOIC-14_3.9x8.7mm_P1.27mm

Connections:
+3V3: C3.1, J2.4 (VDD), U3.2 (VO), U4.14 (VCC)
/A0: J1.13, U1.9 (IO9), U2.11 (A0)
/A1: J1.15, U1.8 (IO8), U2.10 (A1)
/A2: J1.17, U1.25 (IO25), U2.9 (A2)
/A3: J1.11, U1.5 (IO5), U2.8 (A3)
/A4: J1.20, U1.4 (IO4), U2.7 (A4)
/A5: J1.21, U1.44 (IN44/OE1), U2.6 (A5)
/A6: J1.23, U1.2 (IN2), U2.5 (A6)
/A7: J1.25, U1.1 (IN1/GCLR), U2.4 (A7)
/A8: J1.27, U2.29 (A8)
/A9: J1.29, U2.28 (A9)
/A10: J1.31, U2.24 (A10)
/A11: J1.32, U2.27 (A11)
/A12: J1.30, U2.3 (A12)
/A13: J1.28, U2.30 (A13)
/A14: J1.26, U1.20 (IO20)
/A14M: U1.12 (IO12), U2.31 (A14)
/A15: J1.24, U1.16 (IO16)
/A15M: U1.24 (IO24), U2.2 (A15)
/CS: R3.2, U1.26 (IO26)
/D0: J1.10, U1.41 (IO41), U2.13 (O0)
/D1: J1.12, U1.40 (IO40), U2.14 (O1)
/D2: J1.9, U1.39 (IO39), U2.15 (O2)
/D3: J1.16, U1.37 (IO37), U2.18 (O3)
/D4: J1.18, U1.36 (IO36), U2.19 (O4)
/D5: J1.19, U1.34 (IO34), U2.20 (O5)
/D6: J1.14, U1.33 (IO33), U2.21 (O6)
/D7: J1.22, U1.31 (IO31), U2.22 (O7)
/MISO: U1.28 (IO28), U4.6
/MOSI: R1.2, U1.29 (IO29)
/PHI2: J1.3, U1.18 (IO18)
/ROM_CE: U1.14 (IO14), U2.23 (~CE)
/ROM_OE: U1.6 (IO6), U2.25 (~OE~/VPP)
/R_~W: J1.7, U1.11 (IO11)
/SCK: R2.2, U1.27 (IO27)
/~IO: J1.5, U1.17 (IO17)
/~IOCTRL: J1.6, U1.21 (IO21)
/~IRQ: J1.8
/~MAP: J1.1
/~RESET: J1.4, U1.19 (IO19)
GND: C1.2, C2.1, C3.2, J1.2, J1.34, J2.3 (VSS), J2.6 (VSS), J2.12 (SHELL1), J2.13 (SHELL2), U1.10 (GND), U1.22 (GND), U1.30 (GND), U1.42 (GND), U2.16 (GND), U3.1 (GND), U4.1, U4.4, U4.7 (GND), U4.10, U4.13
unnamed: J2.1 (CD/DAT3), U4.8
unnamed: J2.2 (CMD), U4.3
unnamed: J2.5 (CLK), U4.11
unnamed: J2.7 (DAT0), R4.1
unnamed: R1.1, U4.2
unnamed: R2.1, U4.12
unnamed: R3.1, U4.9
unnamed: R4.2, U4.5
VCC: C1.1, C2.2, J1.33, U1.3 (VCC), U1.15 (VCC), U1.23 (VCC), U1.35 (VCC), U2.32 (VCC), U3.3 (VI)

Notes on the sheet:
[3F3]

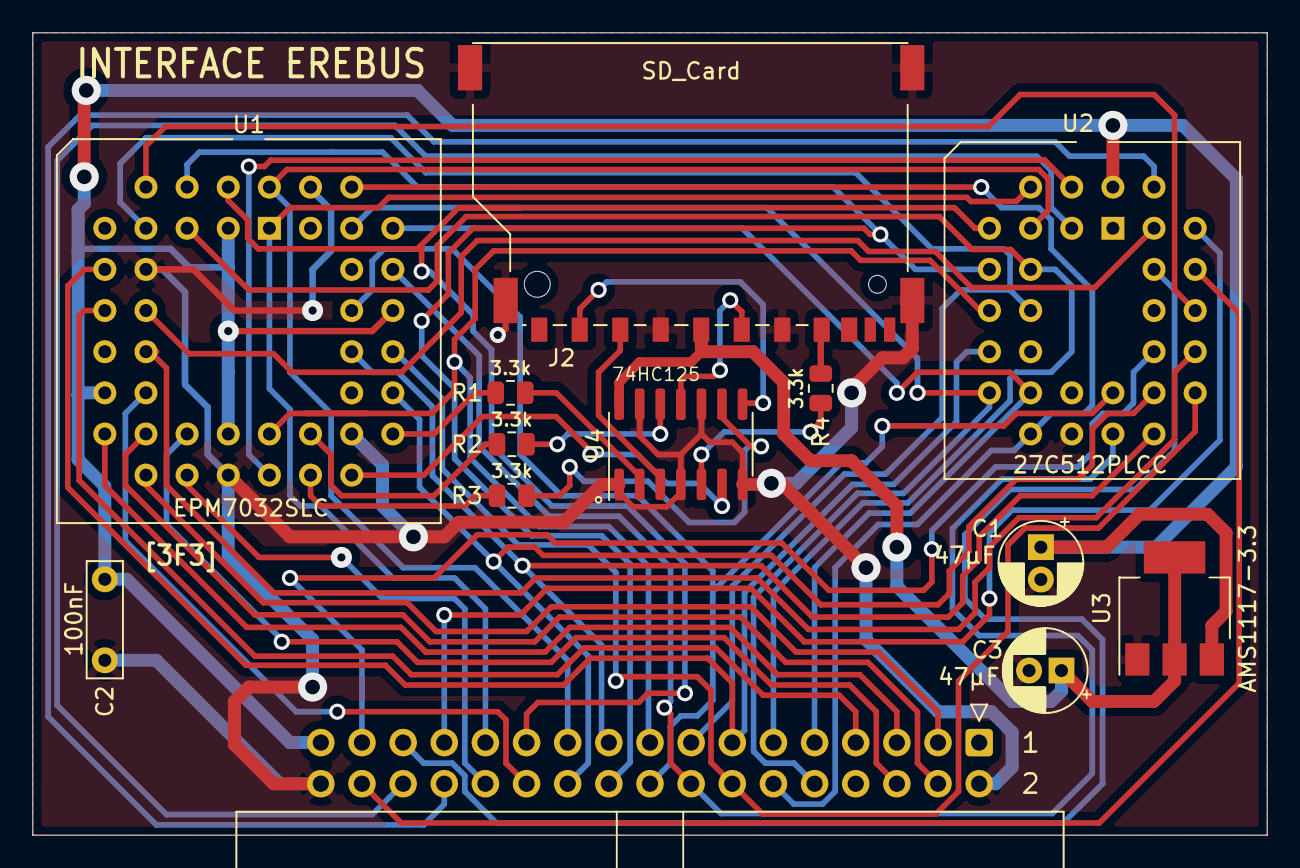
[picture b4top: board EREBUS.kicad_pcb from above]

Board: 2 copper layers, 76.2 x 49.5 mm, 13 parts (0 on the bottom side), 48 nets.
